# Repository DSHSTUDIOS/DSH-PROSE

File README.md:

# DSH-Prose

A handheld e-paper reader and sketchpad I designed as a birthday gift for Dwig. I wanted to make something personal that he could actually use to read, take notes, and sketch. It has a 7.5-inch touchscreen, three front buttons, a custom ESP32-S3 board, and a curved case with a clip for a stylus.

## How to use it

1. Format a microSD card as FAT32 and put plain-text books in a folder called `books`. Insert it before powering on.
2. In **Reader**, tap a book and swipe to turn pages. Use the bookmark button to mark your place, or tap a paragraph to attach a handwritten note.
3. In **Scribe**, tap **+** to add a page or **Paper** to change its template. Completed strokes autosave. The **Save** button also exports the ink as a BMP.
4. Tap the sliders icon for Settings. Pick a font, including OpenDyslexic, change text size and line spacing, or switch between light and dark.

The front buttons are **Prev/Clear**, **Mode**, and **Next/Save**. Tap Mode to switch between reading and writing, or hold it to return to the library. The side switch puts the device in **Run** or **Charge**.

## Design screenshots

### Full 3D assembly

[Open-case Fusion view with the populated PCB](assets/DSH-Prose-Fusion-Assembly.png) · [Native Fusion archive](cad/DSH-Prose-Assembly.f3d)

### Rev D PCB

### Schematic

## Project files

| What | Where |
| --- | --- |
| Enclosure and electronics assembly | [Fusion .f3d](cad/DSH-Prose-Assembly.f3d) · [assembly STEP](cad/DSH-Prose-Side-Stylus.step) · [individual STEP and STL parts](cad/) |
| PCB sources | [KiCad project](hardware/DSH-Prose.kicad_pro) · [schematic](hardware/DSH-Prose.kicad_sch) · [board](hardware/DSH-Prose.kicad_pcb) · [project view settings](hardware/DSH-Prose.kicad_prl) |
| Fabrication and assembly | [Gerbers and drill files](hardware/gerbers.zip) · [SMT positions](hardware/DSH-Prose-Positions.csv) · [BOM with purchase links](BOM.csv) |
| Wiring and checks | [Power, pinout and display harness](hardware/README.md) · [ERC and DRC reports](hardware/verification/) |
| Firmware | [C++ source](firmware/) · [PlatformIO configuration](platformio.ini) |
| Product imagery | [Blender scene](assets/DSH-Prose-Studio.blend) |

For the enclosure, print one front frame, one back, three keycaps, and two TPU stylus clips. See the [assembly notes](cad/README.md) for fit and hardware details.

## Build the firmware

Install [PlatformIO Core](https://docs.platformio.org/en/latest/core/installation/index.html), then run these from the repository root:

```sh
pio run
pio run -t upload
pio device monitor
```

The board target is the bare ESP32-S3-WROOM-1-N8R2 module. Flash over USB with a battery attached and the switch set to **RUN**. If USB upload can't enter the loader, hold BOOT, tap RESET, release BOOT, then retry.

**Status:** Design submission. The Rev D PCB passes KiCad ERC and DRC, and the firmware builds. The physical prototype, display and touch bring-up, battery and harness fit, and power-loss testing are still pending. The images above come from the CAD and KiCad files.

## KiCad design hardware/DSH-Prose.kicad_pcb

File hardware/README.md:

# DSH-Prose · Rev D · 7.5-inch touch

A pocket e-paper reader and sketchpad. The carrier board has a 170.2 × 111.2 mm main body and extends up to 11.2 mm past the display at the three front-button positions. It is 1.0 mm thick, with two copper layers and four 2.2 mm mounting holes. The ESP32-S3-WROOM-1-N8R2 RF module mounts directly to the board and has 8 MB flash, 2 MB quad PSRAM, and an on-module antenna that overhangs the right edge. Keep the display backing, battery, fasteners and metal enclosure features clear of the antenna area. The front silkscreen reads “made by pratik dash” and “happy birthday dwig <3)”. [Espressif module pinout and layout guidance](https://www.espressif.com/sites/default/files/documentation/esp32-s3-wroom-1_wroom-1u_datasheet_en.pdf)

Rev D targets the **Good Display GDEY075T7-T01**, a 7.5-inch, 800 × 480 monochrome e-paper panel with bonded five-point capacitive touch. The UC8179 display uses four-wire SPI and the GT911 uses I²C. The panel body is **170.2 × 111.2 × 2.13 mm**. Its active area is **163.2 × 97.92 mm**. The assembly is sized around that panel, with the carrier mounted behind it and three button extensions below it. [Good Display product specification](https://www.good-display.com/product/483.html) · [Good Display outline and touch-flex drawing](https://www.laskakit.cz/user/related_files/gdey075t7-t01.pdf)

Good Display quotes approximately 0.3 s for partial refresh, 1.5 s for fast refresh, and 3 s for full refresh. Capture touch points continuously and draw accumulated strokes in partial updates. Use a finger or a capacitive stylus. GT911 touch provides position without pen pressure. One packed 1-bit framebuffer uses 48,000 bytes, so two use 96,000 bytes. [Good Display product specification](https://www.good-display.com/product/483.html)

A reseller lists panel and kit variants. Good Display’s storefront and LaskaKit showed the panel out of stock when checked. Confirm availability and whether the seller includes an adapter before ordering. [ESP32s listing](https://esp32s.com/product/7-5-inch-e-ink-screen-module-4-grayscale-800x480-e-paper-raspberry-pi-touch-display/) · [Good Display storefront](https://www.buy-lcd.com/products/gdey075t7-t01) · [LaskaKit listing](https://www.laskakit.cz/en/good-display-gdey075t7-t01-7-5--800x480-epaper-displej-grayscale-dotykovy/)

## KiCad files

The schematic and routed PCB use KiCad 9 format and were checked with KiCad 9.0.8. The packaged ERC and DRC reports show zero violations, zero disconnected PCB pads and zero PCB-to-schematic mismatches. J3 and the ESP32 pin assignments carry over from Rev A. R13/R14 are 4.7 kΩ for the touch harness. There are no per-item rule exclusions. Rev D preserves all 198 pin connections from Rev C. SW4, SW5 and SW6 are top-actuated XUNPU TS-1088-AR02016 switches on the screen-facing PCB side (B.Cu). BOOT and RESET use the edge-actuated Alps SKRTLAE010. Assembly requires placing SW4–SW6 on the second side.

Keep both library tables, the symbol library and the `DSH_Prose.pretty` directory beside the project. Keep the `3dmodels` directory beside the board. The PCB 3D view uses the supplied USB-C receptacle, MSK12C02 switch and TS3USB221A models, a dimensioned JST-PH housing model based on the JST drawing, and standard KiCad models for the other components. The USB-C footprint uses a VRML conversion of the supplied STL. The source STL is included, and a simplified STEP with matching envelope dimensions is available for mechanical exports. [JST PH series drawing](https://s3.amazonaws.com/snapeda/datasheet/B2B-PH-SM4-TB_JST.pdf)

The layout targets two-layer 1 oz FR-4, with mostly 0.20 mm signal traces and smaller neck-downs. The DRC minima are 0.10 mm trace width/spacing, 0.25 mm copper-to-edge clearance and 0.20 mm finished drill for the module's exposed-pad vias. Confirm the assembler's process for those vias and the USB-C anchor slots. USB is full-speed (12 Mbit/s); USB impedance and signal integrity still need validation on an assembled board with the selected stackup. [JLCPCB PCB capabilities](https://jlcpcb.com/capabilities/pcb-capabilities) · [Espressif USB layout guidance](https://docs.espressif.com/projects/esp-hardware-design-guidelines/en/latest/esp32s3/pcb-layout-design.html)

## Power and interfaces

```text
USB-C J1
  CC1, CC2 --> 5.1k each to GND
  VBUS -----> MCP73831 (U2) --> protected 1S LiPo (J2)
     |             |            |
     |             +--> LED     +--> P-MOSFET Q1 --> AP2112K --> +3V3
     |                                         SW1 controls       |
     +--> VBUS sense --> USB switch /OE        Q1 and charger    +-- U1 ESP32-S3
  D+/D- --> ESD --> USB switch --> 22R each --> GPIO20/19         +-- J3 touch EPD
                                                                  +-- J4 microSD

 U1 SPI2/FSPI ---- MOSI/SCK/CS + DC/RST/BUSY ----> J3 display controller
 U1 I2C ---------- SDA/SCL + INT/RESET ---------> J3 touch controller
 U1 SDMMC slot 1 - CLK/CMD/DAT0 ----------------> J4 microSD
 U1 GPIOs -------- Prev/Clear, Mode, Next/Save and card detect
```

- **RUN** connects the battery through Q1 to the regulator. USB data is available with a charged battery and a connected USB host. SW1 opens the charger PROG return in this position.
- **CHARGE** disconnects the battery from the regulator and grounds the 10 kΩ PROG return. The MCP73831 charges at about 100 mA nominal from USB. The LED indicates that the charger is actively charging. SW1 only switches the MOSFET gate and PROG return. Select a protected 4.20 V single-cell pack whose manufacturer permits at least 120 mA charge and 600 mA pulse discharge. Check the pack's JST-PH polarity against J2 pin 1 (positive). Follow the pack's temperature range. The board has no cell thermistor input. [Microchip MCP73831 datasheet](https://ww1.microchip.com/downloads/en/DeviceDoc/MCP73831-Family-Data-Sheet-DS20001984H.pdf)
- The AP2112K is rated 600 mA. At that load, allow up to 400 mV dropout plus the MOSFET and battery voltage drop. Allow about 3.75 V on VBAT under load as a conservative starting point for full 3.3 V regulation at peaks. Expect reduced usable battery capacity at high loads. Measure rail sag and temperature with the selected module, SD card and battery. Start bring-up with Wi-Fi disabled and keep SD writes separate from display refresh until the measured load budget permits overlap. [Diodes Inc. AP2112 datasheet](https://www.diodes.com/datasheet/download/AP2112.pdf)
- The native USB path includes a VBUS-controlled USB switch. VBUS absent disables the switch. Its powered-off isolation limits current into the USB path when the battery rail is off. The mode switch intentionally provides neither USB-only operation nor charge-while-playing. To enter the ROM downloader, use RUN and USB, hold BOOT, tap RESET, then release BOOT. [TI TS3USB221A datasheet](https://www.ti.com/lit/ds/symlink/ts3usb221a.pdf)

## ESP32-S3 pin-to-pin netlist

Pad numbers below are the physical WROOM-1 module pads. KiCad's full board-level interchange netlist is in `verification/DSH-Prose.net.xml`.

| U1 pad | Module pin | Net | Other endpoint or use |
|---:|---|---|---|
| 1, 40, 41 | GND, GND, exposed pad | GND | Main ground and antenna reference |
| 2 | 3V3 | +3V3 | U3.5 and local 10 µF + 100 nF |
| 3 | EN | CHIP_EN | R6 10 kΩ to 3.3 V, C6 1 µF to GND, SW3 to GND |
| 4 | GPIO4 | SD_DAT0 | J4.7, R16 pull-up |
| 5 | GPIO5 | SD_CMD | J4.3, R15 pull-up |
| 6 | GPIO6 | SD_CLK | J4.5 |
| 7 | GPIO7 | SD_DETECT_N | J4.9 switch, R20 pull-up |
| 8 | GPIO15 | TOUCH_SDA | J3.9, R13 pull-up |
| 9 | GPIO16 | TOUCH_SCL | J3.10, R14 pull-up |
| 10 | GPIO17 | TOUCH_INT | J3.11 |
| 11 | GPIO18 | TOUCH_RST_N | J3.12 |
| 12 | GPIO8 | NC | Spare |
| 13 | GPIO19 | MCU_USB_DM | R10 → U4.2, U4.7 → J1 A7 and B7 |
| 14 | GPIO20 | MCU_USB_DP | R9 → U4.1, U4.8 → J1 A6 and B6 |
| 15 | GPIO3 | NC | Strapping pin left open |
| 16 | GPIO46 | NC | Strapping pin left open |
| 17 | GPIO9 | NC | Spare |
| 18 | GPIO10 | EPD_CS_N | J3.5, R11 pull-up |
| 19 | GPIO11 | EPD_MOSI | J3.3 |
| 20 | GPIO12 | EPD_SCK | J3.4 |
| 21 | GPIO13 | EPD_DC | J3.6 |
| 22 | GPIO14 | EPD_RST_N | J3.7, R12 pull-up |
| 23 | GPIO21 | EPD_BUSY | J3.8 |
| 24 | GPIO47 | NC | Spare |
| 25 | GPIO48 | NC | Spare |
| 26 | GPIO45 | NC | Strapping pin left open |
| 27 | GPIO0 | BOOT_N | R7 10 kΩ to 3.3 V, SW2 to GND |
| 28, 29, 30 | GPIO35, GPIO36, GPIO37 | NC | Reserved for module variant compatibility |
| 31–34 | GPIO38, GPIO39, GPIO40, GPIO41 | NC | Spare |
| 35 | GPIO42 | BTN_NEXT_N | SW6 to GND |
| 36, 37 | GPIO44, GPIO43 | NC | UART0 pins unused |
| 38 | GPIO2 | BTN_MODE_N | SW5 to GND |
| 39 | GPIO1 | BTN_PREV_N | SW4 to GND |

Set the three user buttons to active-low with internal pull-ups. Use SPI2/FSPI for the display and SDMMC slot 1 in 1-bit mode via the ESP32-S3 GPIO matrix. J4 DAT1/2/3 each have a 10 kΩ pull-up and are independent of the display bus. The card-detect switch closes to ground when the card is inserted. Use low-speed SD initialization and validate the operating frequency on the prototype. [Espressif hardware checklist](https://docs.espressif.com/projects/esp-hardware-design-guidelines/en/latest/esp32s3/schematic-checklist.html) · [Espressif SD pull-up requirements](https://docs.espressif.com/projects/esp-idf/en/stable/esp32s3/api-reference/peripherals/sd_pullup_requirements.html) · [Hirose card socket](https://www.hirose.com/en/product/p/CL0609-0031-0-00)

## Display stack and 12-pin harness

Use a **DESPI-C02** 3.3 V boost adapter for the 24-pin e-paper flex. Set its RESE switch to **0.47 Ω** for the UC8179. Use the **LaskaKit e-Paper Touch adapter** with its dedicated GDEY075T7-T01 socket so all six touch conductors are accessible, including INT and RESET. The touch-tail pin numbers below are from Good Display's engineering drawing. Confirm the contact side and continuity at the actual flex before applying power. Use JST GH GHR-12V-S at the carrier end. Run shared 3.3 V and ground to both branches. [DESPI-C02 manual](https://www.laskakit.cz/user/related_files/despi-c02_connector_board_for_e-paper_display_v1-1.pdf) · [Good Display RESE selection table](https://v4.cecdn.yun300.cn/100001_1909185148/Evaluation%20Kit%20for%20E-Paper%20Display%20DEArduino-L%28C02%29.pdf) · [JST GH drawing](https://www.jst-mfg.com/product/pdf/eng/eGH.pdf)

| Carrier J3 | Signal | DESPI-C02 P2 | GT911 touch flex |
|---:|---|---|---|
| 1 | 3.3 V | 1 | 2 VDD |
| 2 | GND | 2 | 1 GND |
| 3 | EPD MOSI | 3 SDI | — |
| 4 | EPD SCK | 4 SCLK | — |
| 5 | EPD CS | 5 CS | — |
| 6 | EPD D/C | 6 D/C | — |
| 7 | EPD RESET | 7 RES | — |
| 8 | EPD BUSY | 8 BUSY | — |
| 9 | Touch SDA | — | 5 SDA |
| 10 | Touch SCL | — | 6 SCL |
| 11 | Touch interrupt | — | 4 INT |
| 12 | Touch RESET | — | 3 RST |

The vendor's sales-page touch table and engineering drawing disagree. Use the engineering drawing's order, **GND, VDD, RST, INT, SDA, SCL**, when counting the actual touch flex contacts 1 to 6. FPC connector numbers can run in the opposite direction from the flex. With the LaskaKit Touch adapter's dedicated GDEY075T7-T01 socket, FPC socket contacts 1–6 correspond to flex contacts 6–1. Wire J3 supply and I²C to the adapter's labeled contacts, INT to JP1.5 and RESET to the RST side of C6 (the side connected to R3 and the flex socket). A four-wire Qwiic cable alone cannot carry INT and RESET. If using this adapter, open its I2C_PULLUP jumper so the carrier's pull-ups set the bus. [Manufacturer panel drawing](https://www.laskakit.cz/user/related_files/gdey075t7-t01.pdf) · [LaskaKit touch adapter schematic](https://raw.githubusercontent.com/LaskaKit/ESPink/main/HW/touch-adapter/E-paper-touch-adapter.pdf) · [DESPI-C02 schematic](https://www.laskakit.cz/user/related_files/despi-c02_sch_v1-0.pdf)

For firmware bring-up, start SPI at a low clock rate in mode 0 and wait while UC8179 BUSY is low. Start I²C at 100 kHz. Use GPIO18 for GT911 RESET and briefly drive GPIO17 as an output during address selection. Hold INT low across reset to select the 7-bit address 0x5D, complete the controller's reset timing, then make GPIO17 a floating input. Rotate touch coordinates together with the display, and check all four corners. [Good Display GDEY075T7 datasheet](https://p.globalsources.com/IMAGES/PDT/SPEC/751/K1200241751.pdf) · [Goodix GT911 programming guide](https://www.topwaydisplay.com/sites/default/files/2025-05/GT911.pdf)

## Bare-panel adapter reference

For an integrated display adapter, follow the GDEY075T7 reference circuit for its 24-pin e-paper tail and the GDEY075T7-T01 drawing for the separate 6-pin GT911 tail. Copy the documented GDR/RESE boost loop and its high-voltage bypass network. The custom adapter must follow the panel-specific capacitor and NC assignments, which differ from the generic DESPI-C02 connector labels. Keep the high-voltage rails local to the adapter. Tie BS1 low for four-wire SPI and keep the SPI and I²C harness branches short. Confirm both FPC sockets' mating contact orientation against the drawing. [Panel datasheet and reference circuit](https://p.globalsources.com/IMAGES/PDT/SPEC/751/K1200241751.pdf) · [Manufacturer outline](https://www.laskakit.cz/user/related_files/gdey075t7-t01.pdf)

## Enclosure dimensions

The portrait enclosure measures **120.4 × 202 × 18.8 mm** before adding the optional stylus clips. The front button row sits below the display and reads Prev/Clear, Mode, Next/Save from left to right. The left edge has a widened Run/Charge slider opening and tool-access holes for BOOT and RESET. USB-C and microSD are on the right edge. The blue back has the recessed logo and four corner screws. See [enclosure and assembly files](../cad/) for the curved back and side stylus clips.

Print one frame, one back and three copies of [`03-Front-Keycap.stl`](../cad/03-Front-Keycap.stl). Set the frame face down and drop the matching caps into their openings from inside. Their flanges keep them in the frame. Fit the screen into the front ledge with thin perimeter tape. Screw the PCB to the back's standoffs, connect the flexes and battery, and close the back with four M2.5 countersunk screws suited to the printed pilot holes. The back has internal stops that support the button extensions. Check cap movement, switch click, connector access, fastener length, battery and flex fit on a prototype. [Display outline](https://www.laskakit.cz/user/related_files/gdey075t7-t01.pdf)

The separate `3dmodels/GDEY075T7-T01-envelope.step` gives the nominal panel body and active area for a CAD mockup. Flex tails, stiffeners, adapter assemblies, cable bends, and the battery pack require the chosen hardware or the corresponding mechanical drawings.

## ERC in KiCad

1. Open `DSH-Prose.kicad_pro` and launch Schematic Editor. Keep `DSH_PROSE.kicad_sym` and `sym-lib-table` in the same folder.
2. Check each block's nets against this document, especially the two CC resistors and the polarity of GPIO19 D− / GPIO20 D+. Check D+ and D− end to end through R9/R10, U4 and both USB-C contact rows.
3. Verify U1 EN and GPIO0 each have a 10 kΩ pull-up, EN has the 1 µF capacitor, the buttons close to GND, and GPIO3/GPIO45/GPIO46 have no-connect flags.
4. Keep the power flags on external VBUS, GND and SYS_BAT. VBAT and 3.3 V already have a charger and regulator power-output pin on their respective nets. Leave explicit no-connects on unused module pins, the USB SBU pins, the unused USB switch channel and the regulator NC.
5. Select **Inspect → Electrical Rules Checker → Run ERC**. Inspect errors and warnings with the default rule checks. To verify the supplied project from the command line, run `kicad-cli sch erc --severity-all --exit-code-violations DSH-Prose.kicad_sch`. See `verification/ERC.rpt` for the recorded result.
6. If the schematic changes, use **Tools → Update PCB from Schematic**. Run PCB DRC with schematic parity enabled. Check the antenna keepout, the USB signal route, enclosure access to the controls and the display harness length before ordering.

## First article checks

Verify USB VBUS and ground continuity, then measure the battery and rail with the switch both ways. In CHARGE, check the charge current, LED and input isolation. In RUN, verify that the charge current stops. Scope 3.3 V during cold boot, EPD refresh and a sustained microSD write at high and low battery voltage. Test USB enumeration with both orientations of a known data cable. Check the SD detect switch, all five tactile buttons, EPD BUSY behavior and I²C touch coordinates before fixing the case dimensions. Confirm the switch detents agree with the RUN and CHARGE markings and that the selected USB-C plug and microSD card can be fully inserted through the case. Verify the antenna clearance with both the actual screen and the battery in place. The board has not been assembled or bench-tested.

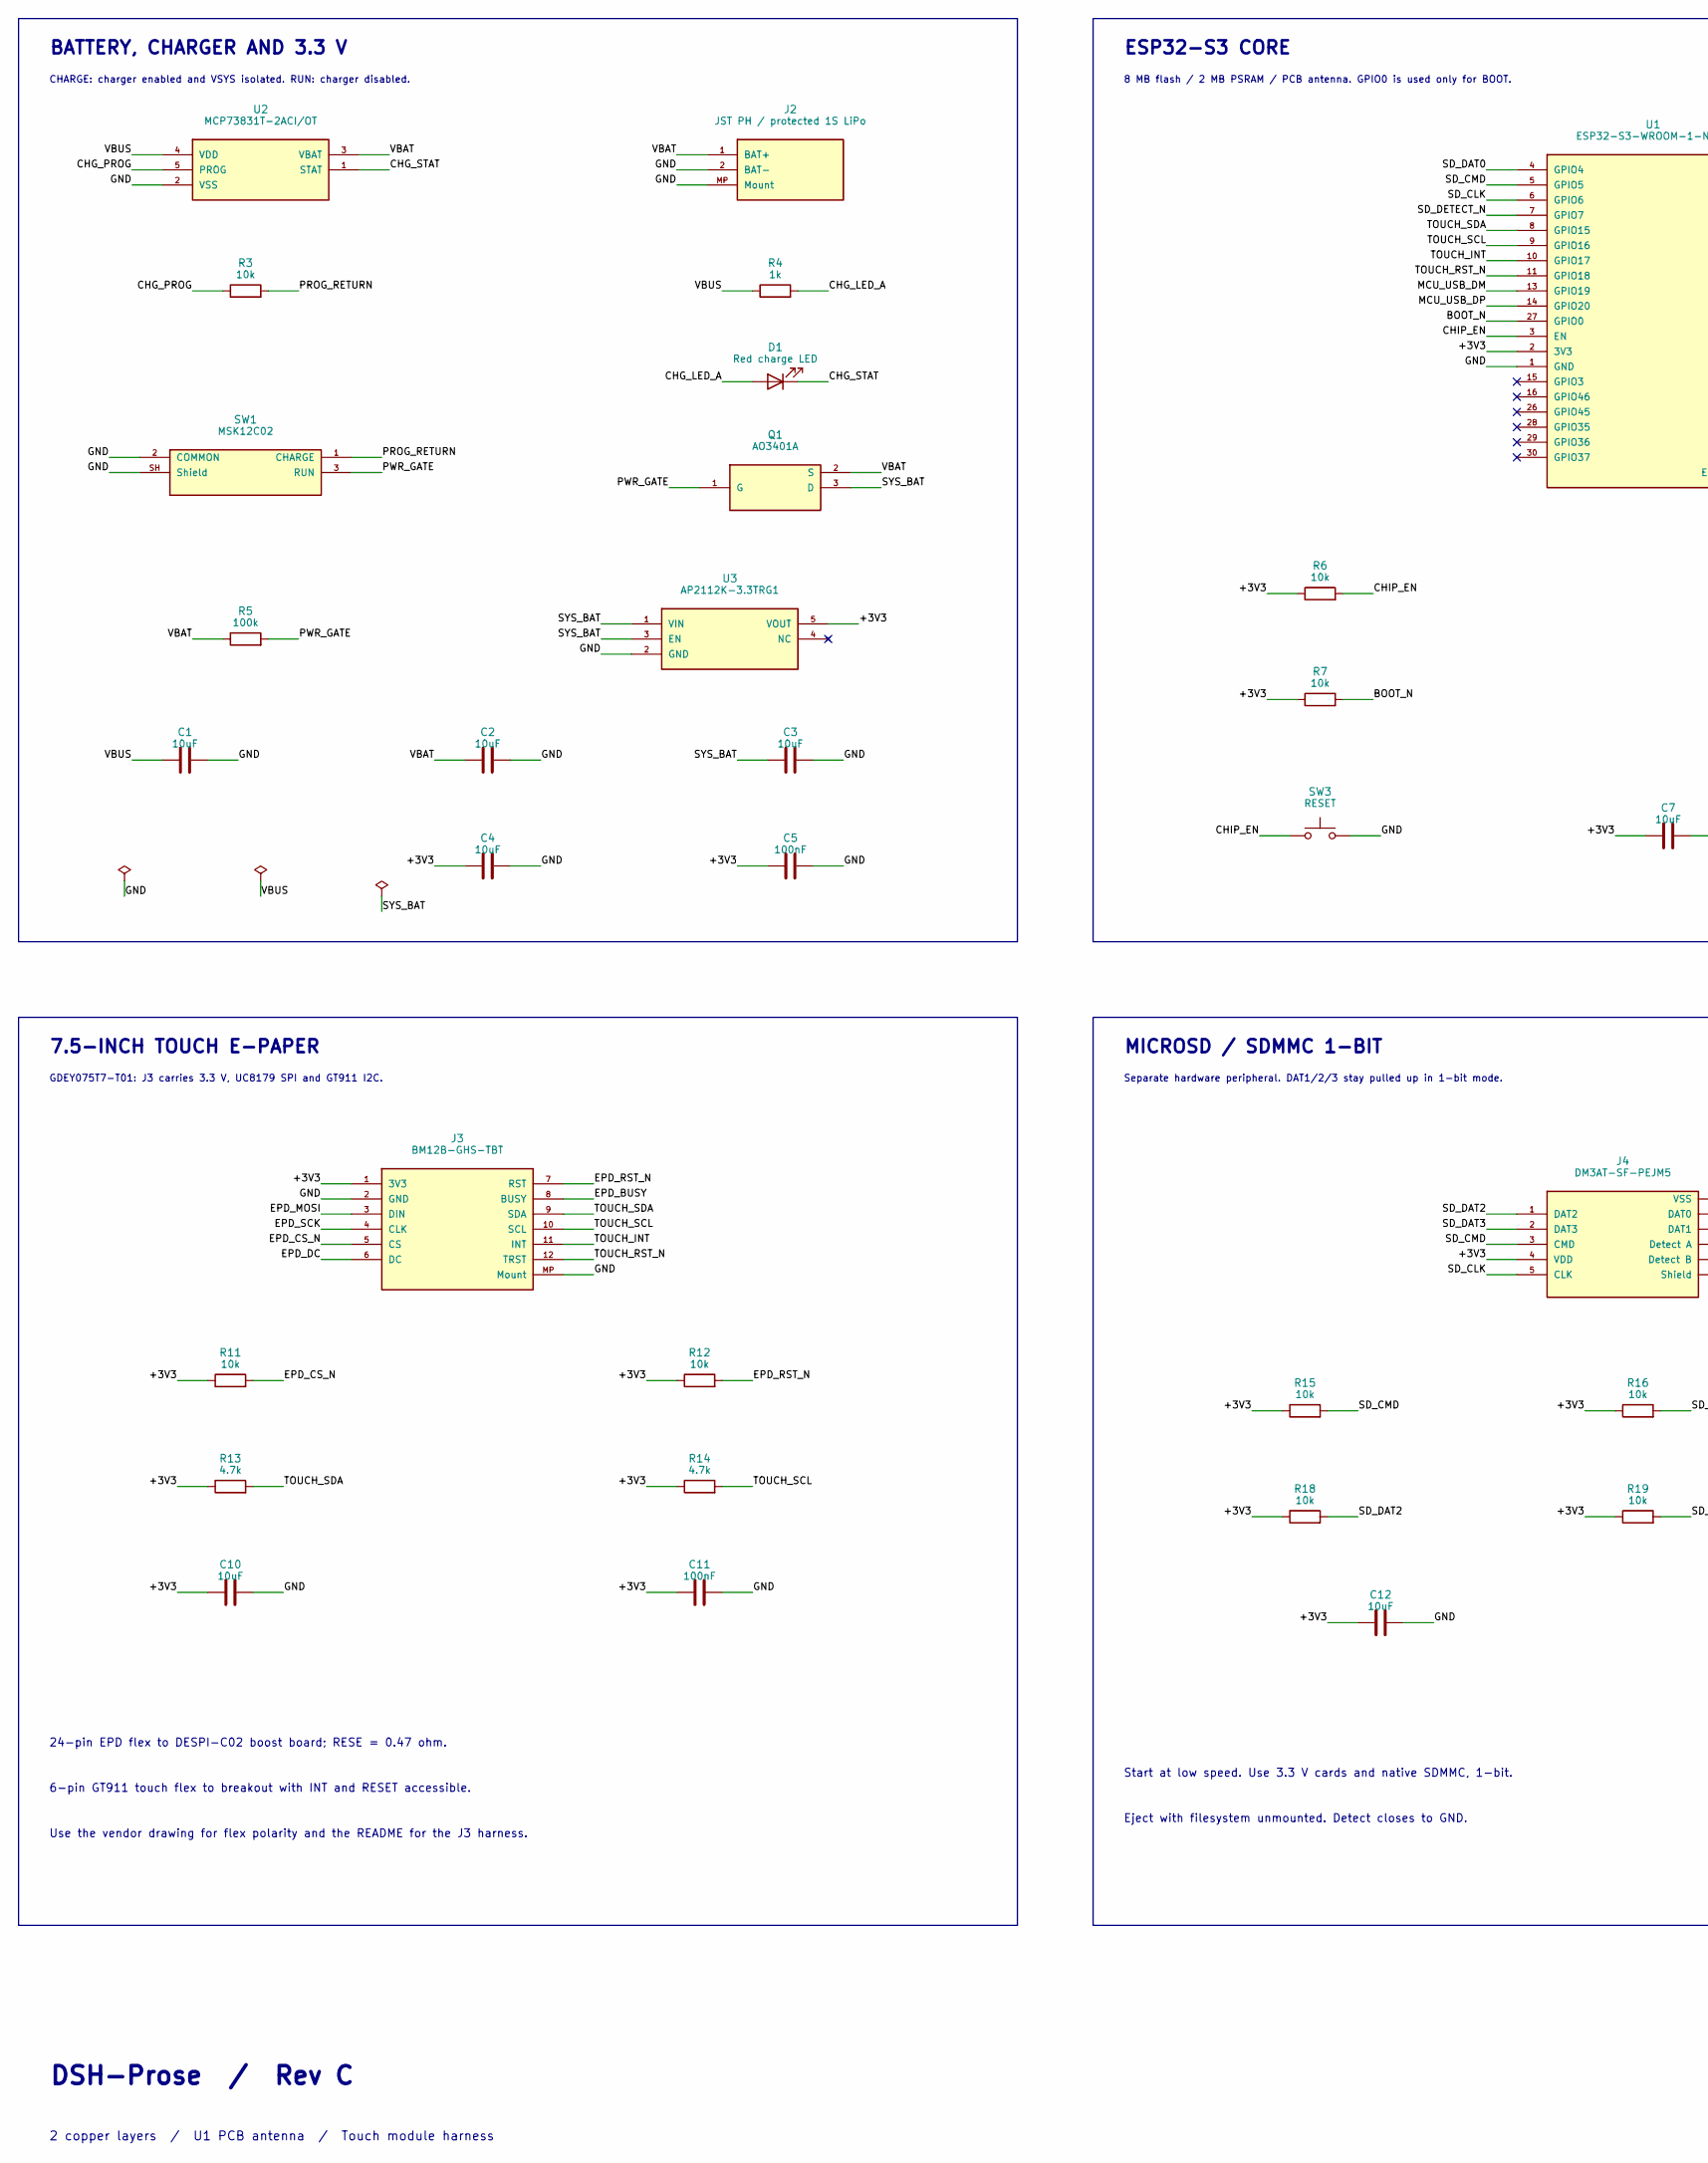
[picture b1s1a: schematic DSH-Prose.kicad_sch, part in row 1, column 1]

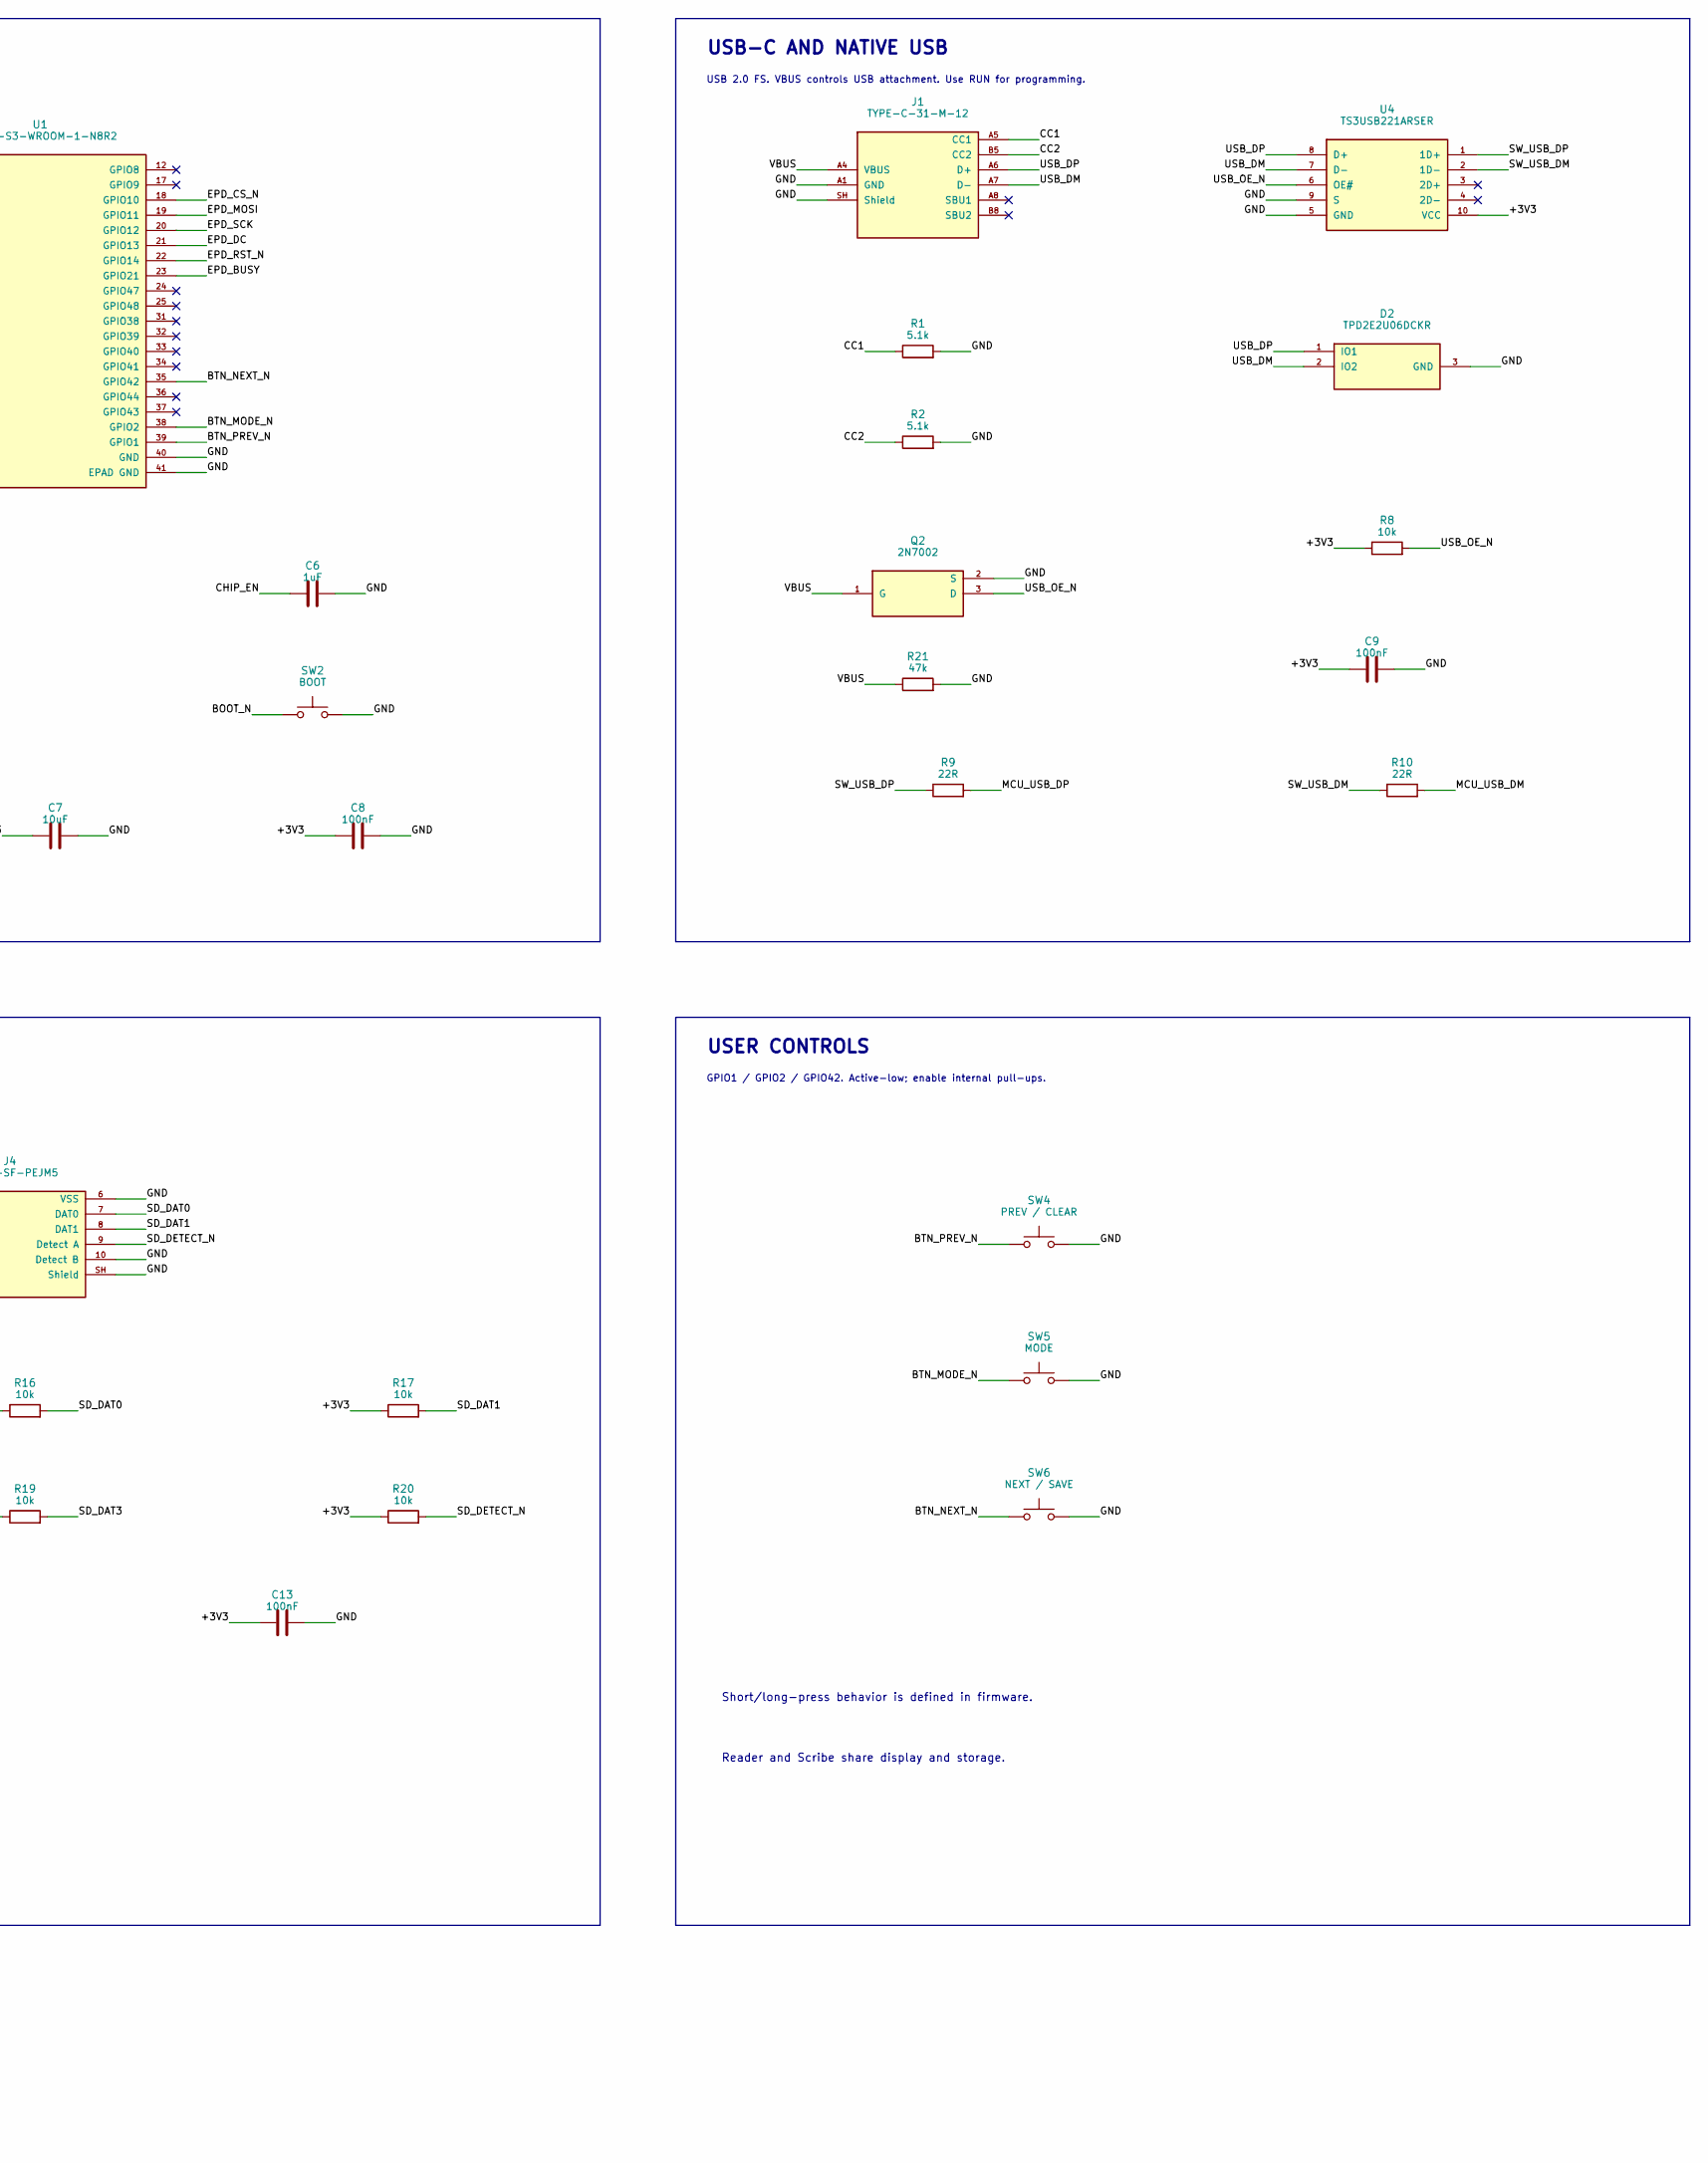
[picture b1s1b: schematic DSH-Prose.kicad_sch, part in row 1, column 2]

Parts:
C1, C2, C3, C4, C7, C10, C12: 10uF; C_0805_2012Metric
C5, C8, C9, C11, C13: 100nF; C_0603_1608Metric
C6: 1uF; C_0603_1608Metric
D1: Red charge LED; LED_0603_1608Metric
D2: TPD2E2U06DCKR; SOT-323_SC-70
J1: TYPE-C-31-M-12; USB_C_Receptacle_HRO_TYPE-C-31-M-12
J2: JST PH / protected 1S LiPo; JST_PH_B2B-PH-SM4-TB_1x02-1MP_P2.00mm_Vertical
J3: BM12B-GHS-TBT; JST_GH_BM12B-GHS-TBT_1x12-1MP_P1.25mm_Vertical
J4: DM3AT-SF-PEJM5; microSD_HC_Hirose_DM3AT-SF-PEJM5
Q1: AO3401A; SOT-23
Q2: 2N7002; SOT-23
R1, R2: 5.1k; R_0603_1608Metric
R3, R6, R7, R8, R11, R12, R15, R16, R17, R18, R19, R20: 10k; R_0603_1608Metric
R4: 1k; R_0603_1608Metric
R5: 100k; R_0603_1608Metric
R9, R10: 22R; R_0603_1608Metric
R13, R14: 4.7k; R_0603_1608Metric
R21: 47k; R_0603_1608Metric
SW1: MSK12C02; SW_SPDT_Shouhan_MSK12C02
SW2: BOOT; SW_Push_1P1T-MP_NO_Horizontal_Alps_SKRTLAE010
SW3: RESET; SW_Push_1P1T-MP_NO_Horizontal_Alps_SKRTLAE010
SW4: PREV / CLEAR; SW_SPST_TS-1088-xR020
SW5: MODE; SW_SPST_TS-1088-xR020
SW6: NEXT / SAVE; SW_SPST_TS-1088-xR020
U1: ESP32-S3-WROOM-1-N8R2; ESP32-S3-WROOM-1
U2: MCP73831T-2ACI/OT; SOT-23-5
U3: AP2112K-3.3TRG1; SOT-23-5
U4: TS3USB221ARSER; Texas_UQFN-10_1.5x2mm_P0.5mm

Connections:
/+3V3: C4.1, C5.1, C7.1, C8.1, C9.1, C10.1, C11.1, C12.1, C13.1, J3.1 (3V3), J4.4 (VDD), R6.1, R7.1, R8.1, R11.1, R12.1, R13.1, R14.1, R15.1, R16.1, R17.1, R18.1, R19.1, R20.1, U1.2 (3V3), U3.5 (VOUT), U4.10 (VCC)
/BOOT_N: R7.2, SW2.1, U1.27 (GPIO0)
/BTN_MODE_N: SW5.1, U1.38 (GPIO2)
/BTN_NEXT_N: SW6.1, U1.35 (GPIO42)
/BTN_PREV_N: SW4.1, U1.39 (GPIO1)
/CC1: J1.A5 (CC1), R1.1
/CC2: J1.B5 (CC2), R2.1
/CHG_LED_A: D1.2 (A), R4.2
/CHG_PROG: R3.1, U2.5 (PROG)
/CHG_STAT: D1.1 (K), U2.1 (STAT)
/CHIP_EN: C6.1, R6.2, SW3.1, U1.3 (EN)
/EPD_BUSY: J3.8 (BUSY), U1.23 (GPIO21)
/EPD_CS_N: J3.5 (CS), R11.2, U1.18 (GPIO10)
/EPD_DC: J3.6 (DC), U1.21 (GPIO13)
/EPD_MOSI: J3.3 (DIN), U1.19 (GPIO11)
/EPD_RST_N: J3.7 (RST), R12.2, U1.22 (GPIO14)
/EPD_SCK: J3.4 (CLK), U1.20 (GPIO12)
/GND: C1.2, C2.2, C3.2, C4.2, C5.2, C6.2, C7.2, C8.2, C9.2, C10.2, C11.2, C12.2, C13.2, D2.3 (GND), J1.A1 (GND), J1.A12, J1.B1, J1.B12, J1.SH (Shield), J2.2 (BAT-), J2.MP (Mount), J3.2 (GND), J3.MP (Mount), J4.6 (VSS), J4.10 (Detect_B), J4.SH (Shield), Q2.2 (S), R1.2, R2.2, R21.2, SW1.2 (COMMON), SW1.SH (Shield), SW2.2, SW3.2, SW4.2, SW5.2, SW6.2, U1.1 (GND), U1.40 (GND), U1.41 (EPAD_GND), U2.2 (VSS), U3.2 (GND), U4.5 (GND), U4.9 (S)
/MCU_USB_DM: R10.2, U1.13 (GPIO19)
/MCU_USB_DP: R9.2, U1.14 (GPIO20)
/PROG_RETURN: R3.2, SW1.1 (CHARGE)
/PWR_GATE: Q1.1 (G), R5.2, SW1.3 (RUN)
/SD_CLK: J4.5 (CLK), U1.6 (GPIO6)
/SD_CMD: J4.3 (CMD), R15.2, U1.5 (GPIO5)
/SD_DAT0: J4.7 (DAT0), R16.2, U1.4 (GPIO4)
/SD_DAT1: J4.8 (DAT1), R17.2
/SD_DAT2: J4.1 (DAT2), R18.2
/SD_DAT3: J4.2 (DAT3), R19.2
/SD_DETECT_N: J4.9 (Detect_A), R20.2, U1.7 (GPIO7)
/SW_USB_DM: R10.1, U4.2 (1D-)
/SW_USB_DP: R9.1, U4.1 (1D+)
/SYS_BAT: C3.1, Q1.3 (D), U3.1 (VIN), U3.3 (EN)
/TOUCH_INT: J3.11 (INT), U1.10 (GPIO17)
/TOUCH_RST_N: J3.12 (TRST), U1.11 (GPIO18)
/TOUCH_SCL: J3.10 (SCL), R14.2, U1.9 (GPIO16)
/TOUCH_SDA: J3.9 (SDA), R13.2, U1.8 (GPIO15)
/USB_DM: D2.2 (IO2), J1.A7 (D-), J1.B7, U4.7 (D-)
/USB_DP: D2.1 (IO1), J1.A6 (D+), J1.B6, U4.8 (D+)
/USB_OE_N: Q2.3 (D), R8.2, U4.6 (OE#)
/VBAT: C2.1, J2.1 (BAT+), Q1.2 (S), R5.1, U2.3 (VBAT)
/VBUS: C1.1, J1.A4 (VBUS), J1.A9, J1.B4, J1.B9, Q2.1 (G), R4.1, R21.1, U2.4 (VDD)

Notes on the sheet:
BATTERY, CHARGER AND 3.3 V
CHARGE: charger enabled and VSYS isolated. RUN: charger disabled.
ESP32-S3 CORE
8 MB flash / 2 MB PSRAM / PCB antenna. GPIO0 is used only for BOOT.
USB-C AND NATIVE USB
USB 2.0 FS. VBUS controls USB attachment. Use RUN for programming.
7.5-INCH TOUCH E-PAPER
GDEY075T7-T01: J3 carries 3.3 V, UC8179 SPI and GT911 I2C.
24-pin EPD flex to DESPI-C02 boost board; RESE = 0.47 ohm.
6-pin GT911 touch flex to breakout with INT and RESET accessible.
Use the vendor drawing for flex polarity and the README for the J3 harness.
MICROSD / SDMMC 1-BIT
Separate hardware peripheral. DAT1/2/3 stay pulled up in 1-bit mode.
Start at low speed. Use 3.3 V cards and native SDMMC, 1-bit.
Eject with filesystem unmounted. Detect closes to GND.
USER CONTROLS
GPIO1 / GPIO2 / GPIO42. Active-low; enable internal pull-ups.
Short/long-press behavior is defined in firmware.
Reader and Scribe share display and storage.
DSH-Prose / Rev C
2 copper layers / U1 PCB antenna / Touch module harness

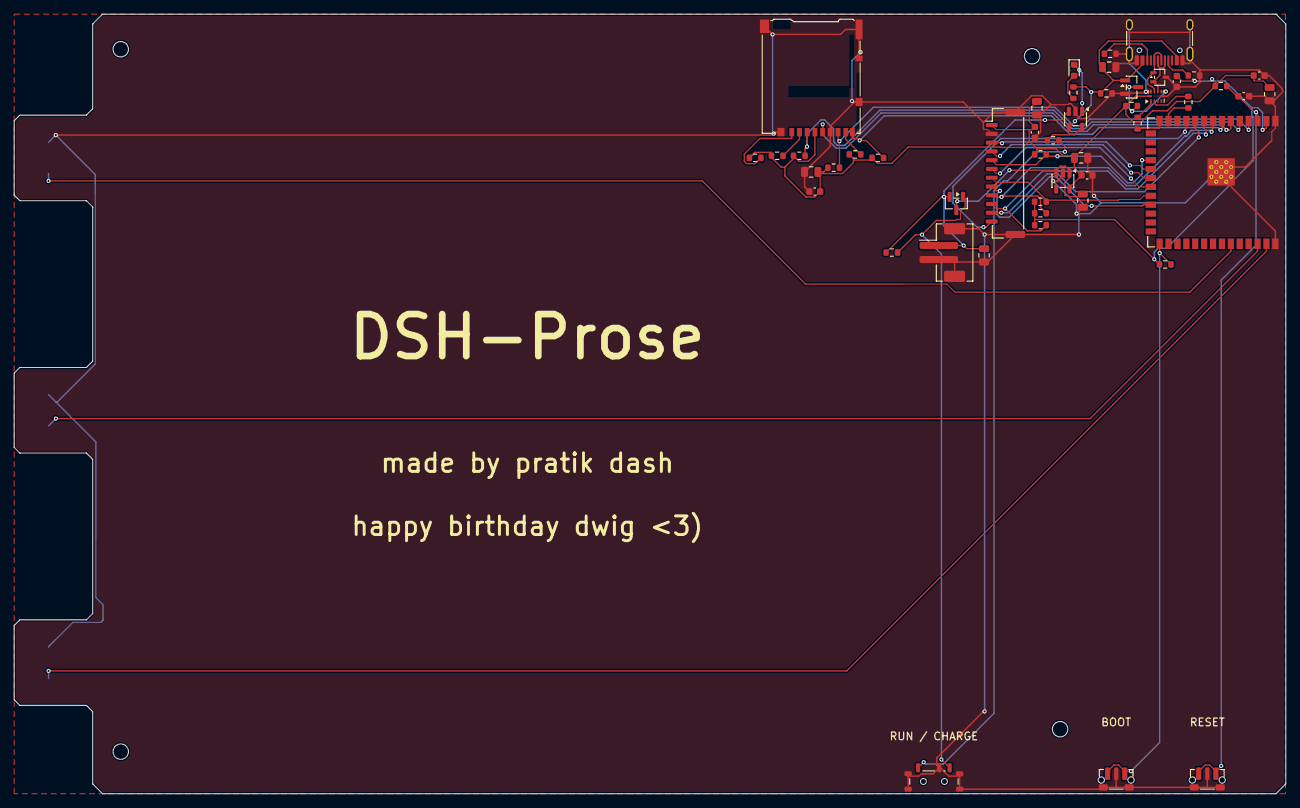
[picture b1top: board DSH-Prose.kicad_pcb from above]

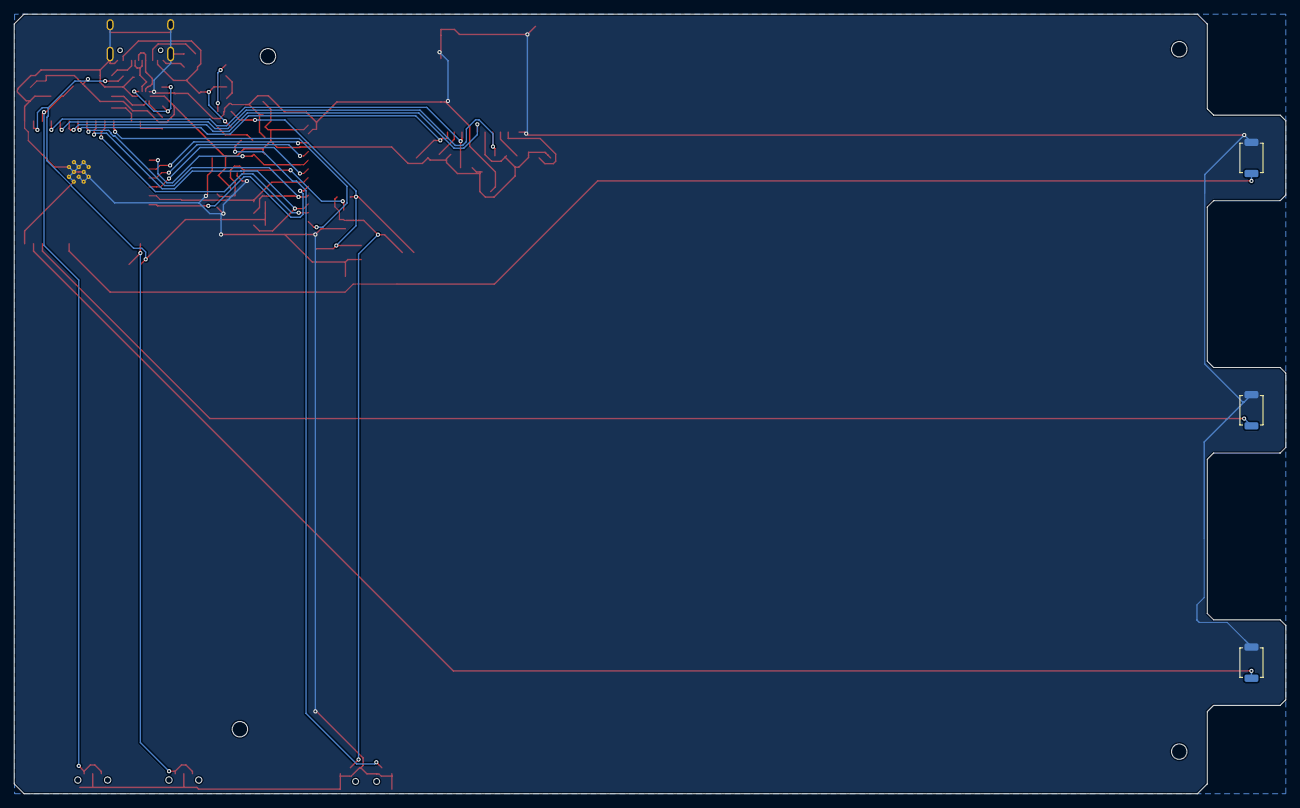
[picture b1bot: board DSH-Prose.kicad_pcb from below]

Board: 2 copper layers, 181.4 x 111.2 mm, 52 parts (3 on the bottom side), 41 nets.

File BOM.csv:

Category,Designators,Item,Qty per device,Unit,Owned,Manufacturer part or spec,Package or material,LCSC,Purchase link,Notes
Fabrication,PCB1,Custom Rev D bare PCB,1,board,No,DSH-Prose Rev D,"2-layer FR-4, 1.0 mm, 1 oz, lead-free HASL",,https://jlcpcb.com/PCBQuote,Upload hardware/gerbers.zip. Check the 0.20 mm drill capability before ordering.
Fabrication,PCBA1,Two-sided PCB assembly,1,service,No,Standard PCBA,Front and back SMT,,https://jlcpcb.com/pcb-assembly,"PCB component rows are placements for the same board. Check stock, vendor rotations and any customer-supplied parts when quoting."
PCB component,U1,ESP32-S3 RF module,1,piece,No,ESP32-S3-WROOM-1-N8R2,25.5 x 18 mm module,C2913204,https://www.lcsc.com/product-detail/C2913204.html,"8 MB flash, 2 MB QSPI PSRAM and on-module antenna."
PCB component,U2,4.2 V LiPo charger,1,piece,No,MCP73831T-2ACI/OT,SOT-23-5,C424093,https://www.lcsc.com/product-detail/C424093.html,
PCB component,U3,3.3 V regulator,1,piece,No,AP2112K-3.3TRG1,SOT-23-5,C51118,https://www.lcsc.com/product-detail/C51118.html,
PCB component,U4,USB data switch,1,piece,No,TS3USB221ARSER,"UQFN-10, RSE",C128396,https://www.lcsc.com/product-detail/C128396.html,
PCB component,D1,Red charge LED,1,piece,No,KT-0603R,0603,C2286,https://www.lcsc.com/product-detail/C2286.html,
PCB component,D2,Dual USB ESD protection,1,piece,No,TPD2E2U06DCKR,SC70-3,C1855726,https://www.lcsc.com/product-detail/C1855726.html,
PCB component,Q1,P-channel MOSFET,1,piece,No,AO3401A,SOT-23,C15127,https://www.lcsc.com/product-detail/C15127.html,
PCB component,Q2,N-channel MOSFET,1,piece,No,2N7002,SOT-23,C8545,https://www.lcsc.com/product-detail/C8545.html,
PCB component,J1,USB-C USB 2.0 receptacle,1,piece,No,TYPE-C-31-M-12,16-pin SMT,C165948,https://www.lcsc.com/product-detail/C165948.html,
PCB component,J2,Battery header,1,piece,No,B2B-PH-SM4-TB(LF)(SN),"JST PH 2.0 mm, 2 pin SMT",C160352,https://www.lcsc.com/product-detail/C160352.html,
PCB component,J3,Display harness header,1,piece,No,BM12B-GHS-TBT,"JST GH 1.25 mm, 12 pin SMT",,https://www.digikey.com/en/products/detail/jst-sales-america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,
PCB component,J4,Push-push microSD socket,1,piece,No,DM3AT-SF-PEJM5,SMT with card detect,C114218,https://www.lcsc.com/product-detail/C114218.html,
PCB component,SW1,Run/Charge slide switch,1,piece,No,MSK12C02,SPDT SMT,C431540,https://www.lcsc.com/product-detail/C431540.html,
PCB component,"SW2,SW3",Boot and reset switches,2,piece,No,SKRTLAE010,Side-actuated SMT,C110293,https://www.lcsc.com/product-detail/C110293.html,
PCB component,"SW4,SW5,SW6",Front user button switches,3,piece,No,TS-1088-AR02016,Top-actuated SMT,C720477,https://www.lcsc.com/product-detail/C720477.html,Place on the back copper side toward the display.
PCB component,"C1,C2,C3,C4,C7,C10,C12","10 uF, 25 V, X5R",7,piece,No,CL21A106KAYNNNE,0805,C15850,https://www.lcsc.com/product-detail/C15850.html,
PCB component,"C5,C8,C9,C11,C13","100 nF, 50 V, X7R",5,piece,No,CC0603KRX7R9BB104,0603,C14663,https://www.lcsc.com/product-detail/C14663.html,
PCB component,C6,"1 uF, 25 V, X7R",1,piece,No,CL10B105KA8NNNC,0603,C29936,https://www.lcsc.com/product-detail/C29936.html,
PCB component,"R1,R2",5.1 kΩ resistor,2,piece,No,0603WAF5101T5E,0603,C23186,https://www.lcsc.com/product-detail/C23186.html,
PCB component,"R3,R6,R7,R8,R11,R12,R15,R16,R17,R18,R19,R20",10 kΩ resistor,12,piece,No,0603WAF1002T5E,0603,C25804,https://www.lcsc.com/product-detail/C25804.html,
PCB component,R4,1 kΩ resistor,1,piece,No,0603WAF1001T5E,0603,C21190,https://www.lcsc.com/product-detail/C21190.html,
PCB component,R5,100 kΩ resistor,1,piece,No,0603WAF1003T5E,0603,C25803,https://www.lcsc.com/product-detail/C25803.html,
PCB component,"R9,R10",22 Ω resistor,2,piece,No,0603WAF220JT5E,0603,C23345,https://www.lcsc.com/product-detail/C23345.html,
PCB component,"R13,R14",4.7 kΩ resistor,2,piece,No,0603WAF4701T5E,0603,C23162,https://www.lcsc.com/product-detail/C23162.html,
PCB component,R21,47 kΩ resistor,1,piece,No,0603WAF4702T5E,0603,C25819,https://www.lcsc.com/product-detail/C25819.html,
Display,DISP1,7.5-inch 800 × 480 touch e-paper panel,1,piece,No,GDEY075T7-T01,UC8179 e-paper and GT911 touch,,https://www.buy-lcd.com/products/gdey075t7-t01,Select the panel-only SKU. Check exact -T01 availability with the seller.
Display,ADP1,24-pin e-paper boost adapter,1,piece,No,DESPI-C02,0.50 mm FPC,,https://www.laskakit.cz/en/good-display-despi-c02-univerzaln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,Use the 0.47 Ω RESE setting. Confirm stock or request a standalone adapter from Good Display.
Display,ADP2,GT911 flex adapter,1,piece,No,LaskaKit e-Paper Touch adapter,Use the dedicated GDEY075T7-T01 socket,,https://www.laskakit.cz/en/laskakit-e-paper-touch-adapter/,Follow the J3 harness table for INT and RESET. Open the onboard pull-up jumper.
Harness,H1,JST GH 12-position plug housing,1,piece,No,GHR-12V-S,1.25 mm pitch,,https://www.digikey.com/en/products/detail/jst-sales-america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,
Harness,H2,Pre-crimped JST GH leads,6,double-ended leads,No,AGHGH28K203,"28 AWG, 203 mm",,https://www.digikey.com/en/products/detail/jst-sales-america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,Cut in half for twelve approximately 100 mm leads. Dry-route before cutting or order longer leads if needed.
Power,BAT1,Protected 1S LiPo battery,1,piece,No,"Adafruit 258, 3.7 V nominal, 1200 mAh","JST-PH, 34 × 62 × 5 mm nominal",,https://www.adafruit.com/product/258,"Verify J2 polarity, cable routing, and clearance with the actual battery."
Storage,SD1,microSDHC memory card,1,piece,No,SanDisk Ultra 16 GB,FAT32,,https://www.sandisk.com/products/memory-cards/microsd-cards/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,Format FAT32 and copy .txt books into /books.
Accessory,USB1,USB-C data cable,1,piece,No,Adafruit 4199 or equivalent data cable,USB-C to USB-C,,https://www.adafruit.com/product/4199,Needed to flash and charge.
Accessory,PEN1,Optional passive capacitive stylus,1,piece,No,Targus AMM01TBUS or equivalent,Look for a barrel near the 9.7 mm CAD reference,,https://us.targus.com/products/stylus-for-tablets-and-smartp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,Example source only. Test the GT911 and clip fit on the actual pen.
Enclosure,CASE1,Front frame print,1,part,No,01-Black-Front-Frame.stl,Matte black nylon or equivalent,,https://jlc3dp.com/,Quote using the STL in cad/.
Enclosure,CASE2,Curved back print,1,part,No,02-Curved-Navy-Back.stl,Translucent navy resin or clear resin with tint,,https://jlc3dp.com/,Confirm dark blue finish and prototype the screw bosses.
Enclosure,CASE3,Front keycap prints,3,parts,No,03-Front-Keycap.stl,Black print material,,https://jlc3dp.com/,Quote three copies. Check the vendor's smallest supported part size.
Enclosure,CASE4,Side stylus clip prints,2,parts,No,04-TPU-Side-Clip.stl,Flexible TPU,,https://craftcloud3d.com/en/p/3d-printing-services,Quote two copies with a supplier that can print these small clips.
Hardware,M1,Case closure screws,4,pieces,No,"M2.5 × 6 mm thread-forming, countersunk",90° flat head for plastic,,https://www.aspenfasteners.com/m2-5-x-6mm-thread-rolling-scr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,"Confirm head diameter, depth and pilot fit on the printed shells."
Hardware,M2,PCB mounting screws,4,pieces,No,"M2 × 4 mm thread-forming, pan head",For 1.68 mm printed pilot holes,,https://www.mcmaster.com/products/metric-thread-forming-screws/,Choose compatible size and verify depth in the back standoffs.
Assembly,T1,Thin perimeter adhesive,1,roll,No,3M 467MP-12-5,0.05 mm adhesive transfer tape,,https://www.digikey.com/en/products/detail/3m-tc/467MP-12-5/2657972,Use narrow strips around the display ledge. Keep clear of the flex tails.
Assembly,T2,Flexible adhesive for stylus clips,1,tube,No,E6000 Clear,Flexible adhesive,,https://www.michaels.com/product/e6000-multipurpose-adhesive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,Test on a spare clip and shell material before assembly.
